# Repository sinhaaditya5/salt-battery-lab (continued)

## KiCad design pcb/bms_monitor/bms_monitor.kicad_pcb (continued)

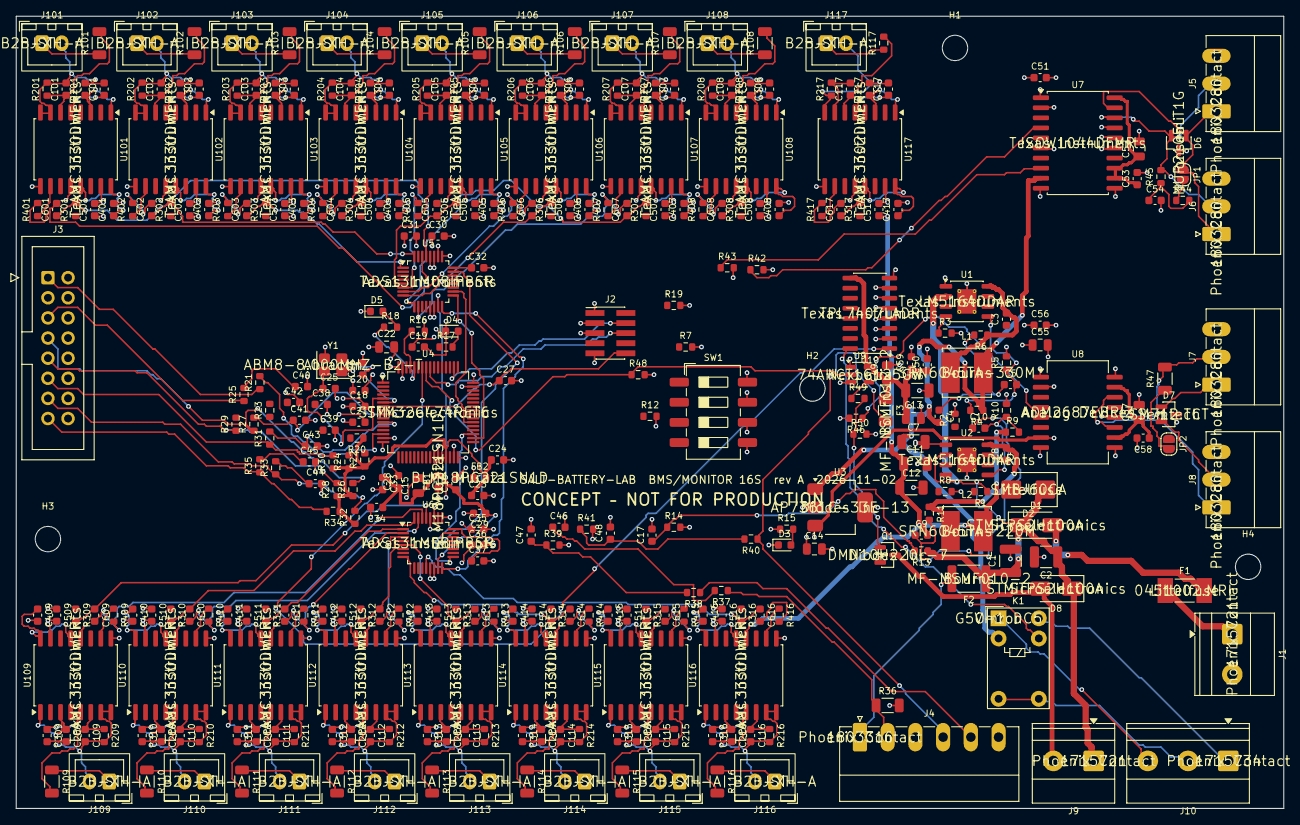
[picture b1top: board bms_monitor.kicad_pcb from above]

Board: 4 copper layers, 160.0 x 100.0 mm, 358 parts (0 on the bottom side), 272 nets.

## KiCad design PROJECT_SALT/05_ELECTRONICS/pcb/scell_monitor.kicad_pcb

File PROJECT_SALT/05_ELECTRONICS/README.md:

# Electronics: SCM-1 salt-cell test monitor (designed for the S-cell chemistry and voltage)

| Item | Status |
|---|---|
| Schematic (`kicad/`, `schematics/`) | 145 parts, 94 nets; **ERC 0 violations** (MAX31856 pin types corrected to datasheet: SDO tri-state, FAULT open-drain, in `scm_pcb.kicad_sym`) |
| PCB (`pcb/`) | 4-layer, 110 × 75 mm; auto-placed, auto-routed **DRAFT**: 1,703 tracks, 37 unrouted connections, 178 clearance errors → **not for fabrication** |
| Gerbers / drill / pick-and-place (`gerbers/`) | exported from the draft, **for review only** |
| BOM (`bom/`) | grouped, with manufacturer part numbers |
| Firmware (`firmware/`) | supervision core + MAX31856 driver + main loop. `make test`: **19/19 core checks, 0 driver failures, main loop syntax-clean under -Werror**. HAL, ADS131M08 and INA228 drivers not written |
| Electrical test procedure | `07_BUILD_MANUAL/acceptance_tests/ELECTRICAL_TEST_PROCEDURE.md` (TP-E01…E06) |

**Design basis** (`params/scell_params.py`, generated `firmware/limits.h`):
- 1.65 / 2.95 V cell trips (inside the 1.58 / 3.05 V side reactions);
- 290 °C hardware thermocouple trip;
- 2 °C/min ramp limit;
- 181 mA (40 mA/cm²) over-current trip.

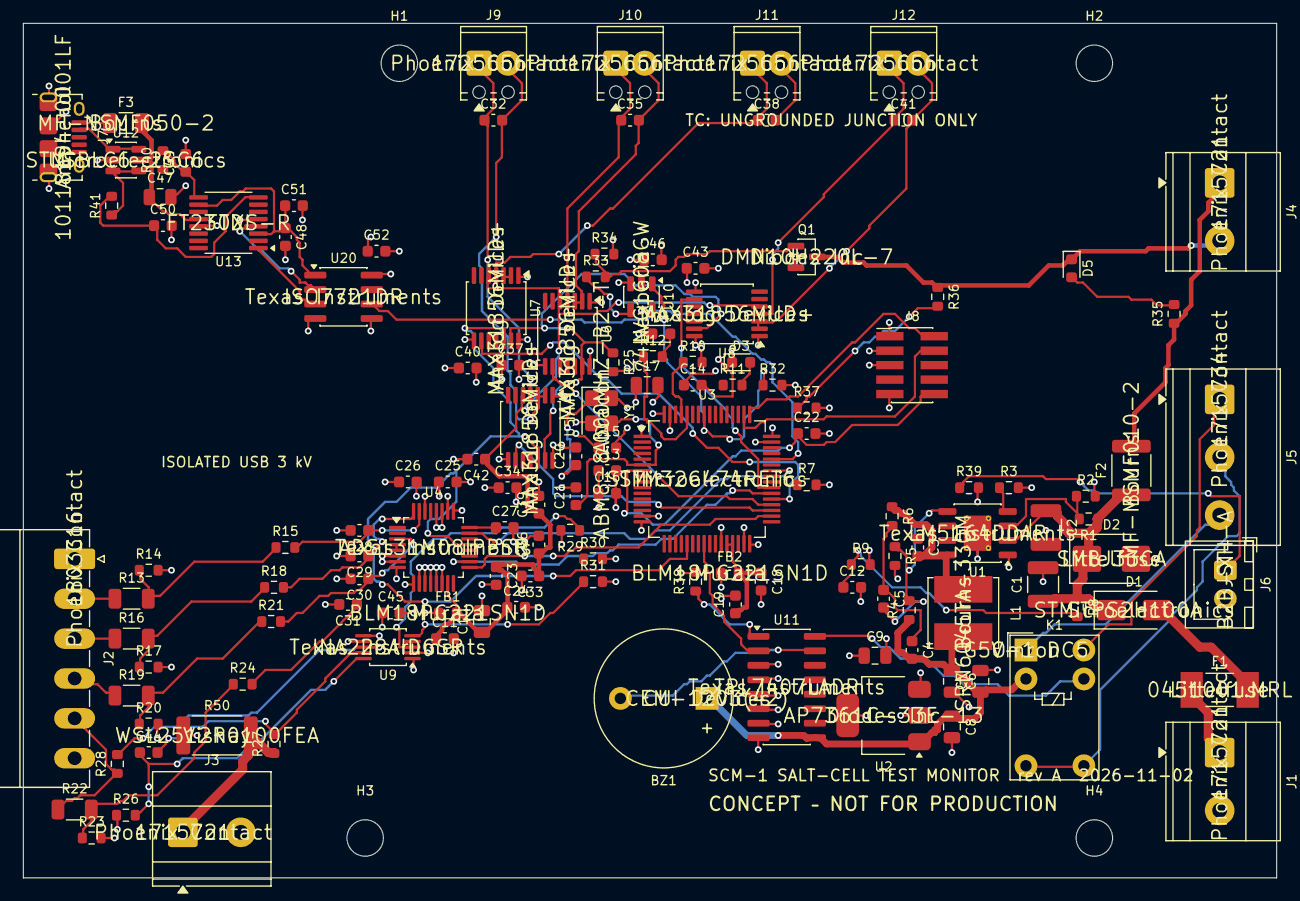
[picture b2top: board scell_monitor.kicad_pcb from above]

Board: 4 copper layers, 110.0 x 75.0 mm, 139 parts (0 on the bottom side), 94 nets.

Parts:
BZ1: CEM-1203(42); Buzzer_12x9.5RM7.6
C1, C2: 2.2u 100V; C_1210_3225Metric
C3: 2.2n; C_0603_1608Metric
C4: 3.3n; C_0603_1608Metric
C5: 56p C0G; C_0603_1608Metric
C6, C7: 22u 10V; C_0805_2012Metric
C8, C9, C10: 10u; C_0805_2012Metric
C11, C12, C13, C14, C15, C16, C19, C22, C24, C26, C33, C34, C36, C37, C39, C40, C42, C43, C45, C46, C48, C51, C52: 100n; C_0603_1608Metric
C17, C47: 4.7u; C_0805_2012Metric
C18, C23, C25: 1u; C_0603_1608Metric
C20, C21: 27p C0G; C_0603_1608Metric
C27: 220n; C_0603_1608Metric
C28, C29, C30, C31: 100n C0G; C_0603_1608Metric
C32, C35, C38, C41, C44: 10n C0G; C_0603_1608Metric
C49, C50: 47p C0G; C_0603_1608Metric
D1: STPS2H100A; D_SMA
D2: SMBJ33CA; D_SMB
D3: green RUN; LED_0603_1608Metric
D4: red FAULT; LED_0603_1608Metric
D5: amber HEAT; LED_0603_1608Metric
F1: 1A; Fuse_Littelfuse-NANO2-451_453
F2: MF-MSMF010-2; Fuse_1812_4532Metric
F3: MF-NSMF050-2; Fuse_1206_3216Metric
FB1, FB2: BLM18PG221SN1D; L_0603_1608Metric
H1, H2, H3, H4: M3; MountingHole_3.2mm_M3
J1: PWR_IN 12-30V; TerminalBlock_Phoenix_MKDS-1,5-2-5.08_1x02_P5.08mm_Horizont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
J2: CELL TAPS; PhoenixContact_MC_1,5_6-G-3.5_1x06_P3.50mm_Horizontal
J3: CYCLER -; TerminalBlock_Phoenix_MKDS-1,5-2-5.08_1x02_P5.08mm_Horizont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
J4: SSR CTRL; TerminalBlock_Phoenix_MKDS-1,5-2-5.08_1x02_P5.08mm_Horizont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
J5: CYCLER INTERLOCK; TerminalBlock_Phoenix_MKDS-1,5-3-5.08_1x03_P5.08mm_Horizont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
J6: E-STOP sense; JST_XH_B2B-XH-A_1x02_P2.50mm_Vertical
J7: USB; USB_Micro-B_Amphenol_10118194_Horizontal
J8: SWD; PinHeader_2x05_P1.27mm_Vertical_SMD
J9: TC1 type-K; TerminalBlock_Phoenix_MPT-0,5-2-2.54_1x02_P2.54mm_Horizontal
J10: TC2 type-K; TerminalBlock_Phoenix_MPT-0,5-2-2.54_1x02_P2.54mm_Horizontal
J11: TC3 type-K; TerminalBlock_Phoenix_MPT-0,5-2-2.54_1x02_P2.54mm_Horizontal
J12: TC4 type-K; TerminalBlock_Phoenix_MPT-0,5-2-2.54_1x02_P2.54mm_Horizontal
K1: G5V-1-DC5; Relay_SPDT_Omron_G5V-1
L1: 33u; L_Bourns_SRN6045TA
Q1: DMN10H220L; SOT-23
R1: 432k; R_0603_1608Metric
R2, R32, R34, R36, R38: 100k; R_0603_1608Metric
R3: 31.6k; R_0603_1608Metric
R4: 158k; R_0603_1608Metric
R5: 49.9k; R_0603_1608Metric
R6: 165k; R_0603_1608Metric
R7, R9, R10, R25, R29, R35, R37, R39: 10k; R_0603_1608Metric
R8: 200k; R_0603_1608Metric
R11, R12, R15, R18, R21, R24, R28: 1k; R_0603_1608Metric
R13, R16, R19, R22: 100k 0.1%; R_1206_3216Metric
R14, R17, R20, R23: 10k 0.1%; R_0603_1608Metric
R26, R27: 10R; R_0603_1608Metric
R30, R31: 4.7k; R_0603_1608Metric
R33: 100R; R_0603_1608Metric
R40, R41: 27R; R_0603_1608Metric
R50: 10m 1% 3W; R_2512_6332Metric
U1: LM5164DDA; HSOP-8-1EP_3.9x4.9mm_P1.27mm_EP2.41x3.1mm_ThermalVias
U2: AP7361C-33E; SOT-223-3_TabPin2
U3: STM32G474RET6; LQFP-64_10x10mm_P0.5mm
U4: ADS131M08IPBS; TQFP-32_5x5mm_P0.5mm
U5, U6, U7, U8: MAX31856MUD; TSSOP-14_4.4x5mm_P0.65mm
U9: INA228AIDGSR; TSSOP-10_3x3mm_P0.5mm
U10: 74LVC1G08; SOT-23-5
U11: TPL7407LAD; SOIC-16_3.9x9.9mm_P1.27mm
U12: USBLC6-2SC6; SOT-23-6
U13: FT230XS; SSOP-16_3.9x4.9mm_P0.635mm
U20: ISO7721DR; SOIC-8_3.9x4.9mm_P1.27mm
Y1: 8MHz; Crystal_SMD_3225-4Pin_3.2x2.5mm

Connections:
+3V3: C9.1, C13.1, C14.1, C15.1, C16.1, C17.1, C25.1, C26.1, C34.1, C37.1, C40.1, C43.1, C45.1, C46.1, C52.1, FB1.1, FB2.1, J8.1, R7.2, R25.2, R29.2, R30.2, R31.2, R39.2, U2.3, U3.1, U3.16, U3.32, U3.48, U3.64, U4.26, U5.8, U6.8, U7.8, U8.8, U9.6, U10.5, U20.8
+3V3_ADC: C10.1, C11.1, C23.1, C24.1, C33.1, C36.1, C39.1, C42.1, FB1.2, U4.15, U5.5, U6.5, U7.5, U8.5
+5V: BZ1.1, C4.2, C6.1, C7.1, C8.1, K1.2, L1.2, R4.1, U2.1, U11.9
A1: C28.1, R15.2, U4.29, U4.31
A2: C29.1, R18.2, U4.2, U4.32
A3: C30.1, R21.2, U4.1, U4.3
A4: C31.1, R24.2, U4.4, U4.5
ADC_CAP: C27.1, U4.24
ADC_CLK: U3.42, U4.23
ADC_CS: U3.34, U4.17
ADC_DRDY: U3.38, U4.18
ADC_SYNC: U3.52, U4.16
BOOT0: R10.1, U3.61
BST1: C3.1, U1.7
BUZ_EN: U3.24, U11.2
BUZ_N: BZ1.2, U11.15
CYC_NEG: J3.1, R27.1, R50.2
EN_UVLO: R1.2, R2.1, U1.3
ESTOP_SNS: J6.1, R39.1, U3.54
FB1: C5.2, R4.2, R5.1, U1.5
GND: C1.2, C2.2, C6.2, C7.2, C8.2, C9.2, C10.2, C11.2, C12.2, C13.2, C14.2, C15.2, C16.2, C17.2, C18.2, C19.2, C20.2, C21.2, C22.2, C23.2, C24.2, C25.2, C26.2, C27.2, C28.2, C29.2, C30.2, C31.2, C33.2, C34.2, C36.2, C37.2, C39.2, C40.2, C42.2, C43.2, C45.2, C46.2, C52.2, D2.2, D3.1, D4.1, J1.2, J2.1, J2.6, J3.2, J6.2, J8.3, J8.5, J8.9, Q1.2, R2.2, R3.2, R5.2, R9.2, R10.2, R14.2, R17.2, R20.2, R23.2, R26.1, R32.2, R34.2, R37.2, R38.2, R50.1, U1.1, U1.9, U2.2, U3.15, U3.27, U3.31, U3.47, U3.63, U4.6, U4.7, U4.8, U4.9, U4.10, U4.11, U4.12, U4.13, U4.14, U4.25, U4.27, U4.28, U4.30, U5.1, U5.14, U6.1, U6.14, U7.1, U7.14, U8.1, U8.14, U9.1, U9.2, U9.7, U10.3, U11.3, U11.4, U11.5, U11.6, U11.7, U11.8, U20.5, Y1.2, Y1.4
HEAT_EN: R32.1, U3.57, U10.1
HEAT_FB: R36.2, R37.1, U3.12
HEAT_G: Q1.1, R33.2, R34.1
HEAT_GATE: R33.1, U10.4
I2C_SCL: R31.1, U3.40, U9.5
I2C_SDA: R30.1, U3.41, U9.4
ILK_COM: J5.2, K1.5, K1.6
ILK_EN: R38.1, U3.58, U11.1
ILK_NC: J5.3, K1.1
ILK_NO: J5.1, K1.10
INA_ALERT: R29.1, U3.53, U9.3
IUSB_3V3: C48.1, C51.1, U13.3, U13.10, U20.1
IUSB_DM: J7.2, R40.1, U12.1, U12.6
IUSB_DP: J7.3, R41.1, U12.3, U12.4
IUSB_FDM: C49.1, R40.2, U13.9
IUSB_FDP: C50.1, R41.2, U13.8
IUSB_GND: C47.2, C48.2, C49.2, C50.2, C51.2, J7.5, J7.SH, U12.2, U13.5, U13.13, U20.4
IUSB_RXD: U13.4, U20.2
IUSB_TXD: U13.1, U20.3
IUSB_VBUS: C47.1, F3.2, U12.5, U13.12
IUSB_VBUS_RAW: F3.1, J7.1
LED_FLT: R12.1, U3.60
LED_FLT_A: D4.2, R12.2
LED_HEAT_A: D5.2, R35.2
LED_RUN: R11.1, U3.59
LED_RUN_A: D3.2, R11.2
NRST: C22.1, J8.10, U3.7
OSC_IN: C20.1, U3.5, Y1.1
OSC_OUT: C21.1, U3.6, Y1.3
PG_5V: R7.1, U1.6, U3.2
RIP1: C4.1, C5.1, R6.2
RLY_COIL: K1.9, U11.16
RON1: R3.1, U1.4
SH_N: C44.2, R27.2, U9.9
SH_P: C44.1, R26.2, U9.10
SPI_MISO: U3.20, U4.20, U5.11, U6.11, U7.11, U8.11
SPI_MOSI: U3.21, U4.21, U5.12, U6.12, U7.12, U8.12
SPI_SCK: U3.19, U4.19, U5.10, U6.10, U7.10, U8.10
SSR_NEG: D5.1, J4.2, Q1.3, R36.1
SSR_POS: F2.2, J4.1, R35.1
SW1: C3.2, L1.1, R6.1, U1.8
SWCLK: J8.4, U3.50
SWDIO: J8.2, U3.49
SWO: J8.6, U3.56
TAP1: J2.2, R13.1
TAP2: J2.3, R16.1
TAP3: J2.4, R19.1
TAP4: J2.5, R22.1, R28.1
TC1_N: C32.2, J9.2, U5.2, U5.3
TC1_P: C32.1, J9.1, U5.4
TC2_N: C35.2, J10.2, U6.2, U6.3
TC2_P: C35.1, J10.1, U6.4
TC3_N: C38.2, J11.2, U7.2, U7.3
TC3_P: C38.1, J11.1, U7.4
TC4_N: C41.2, J12.2, U8.2, U8.3
TC4_P: C41.1, J12.1, U8.4
TC_CS1: U3.35, U5.9
TC_CS2: U3.36, U6.9
TC_CS3: U3.37, U7.9
TC_CS4: U3.39, U8.9
TC_FAULT_N: R25.1, U3.25, U5.13, U6.13, U7.13, U8.13, U10.2
TS1: R13.2, R14.1, R15.1
TS2: R16.2, R17.1, R18.1
TS3: R19.2, R20.1, R21.1
TS4: R22.2, R23.1, R24.1
UART_RX: U3.44, U20.6
UART_TX: U3.43, U20.7
VBUS_S: R28.2, U9.8
VDDA: C18.1, C19.1, FB2.2, U3.28, U3.29
VIN_F: D1.2, F1.2
VIN_P: C1.1, C2.1, D1.1, D2.1, F2.1, R1.1, R8.1, U1.2
VIN_RAW: F1.1, J1.1
VIN_SNS: C12.1, R8.2, R9.1, U3.26

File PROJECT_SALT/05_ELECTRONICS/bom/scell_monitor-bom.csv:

"Reference","Value","Footprint","MPN","Manufacturer","QUANTITY"
"BZ1","CEM-1203(42)","Buzzer_Beeper:Buzzer_12x9.5RM7.6","CEM-1203(42)","CUI Devices","1"
"C1,C2","2.2u 100V","Capacitor_SMD:C_1210_3225Metric","","","2"
"C3","2.2n","Capacitor_SMD:C_0603_1608Metric","","","1"
"C4","3.3n","Capacitor_SMD:C_0603_1608Metric","","","1"
"C5","56p C0G","Capacitor_SMD:C_0603_1608Metric","","","1"
"C6,C7","22u 10V","Capacitor_SMD:C_0805_2012Metric","","","2"
"C8-C10","10u","Capacitor_SMD:C_0805_2012Metric","","","3"
"C11-C16,C19,C22,C24,C26,C33,C34,C36,C37,C39,C40,C42,C43,C45,C46,C48,C51,C52","100n","Capacitor_SMD:C_0603_1608Metric","","","23"
"C17,C47","4.7u","Capacitor_SMD:C_0805_2012Metric","","","2"
"C18,C23,C25","1u","Capacitor_SMD:C_0603_1608Metric","","","3"
"C20,C21","27p C0G","Capacitor_SMD:C_0603_1608Metric","","","2"
"C27","220n","Capacitor_SMD:C_0603_1608Metric","","","1"
"C28-C31","100n C0G","Capacitor_SMD:C_0603_1608Metric","","","4"
"C32,C35,C38,C41,C44","10n C0G","Capacitor_SMD:C_0603_1608Metric","","","5"
"C49,C50","47p C0G","Capacitor_SMD:C_0603_1608Metric","","","2"
"D1","STPS2H100A","Diode_SMD:D_SMA","STPS2H100A","STMicroelectronics","1"
"D2","SMBJ33CA","Diode_SMD:D_SMB","SMBJ33CA","Littelfuse","1"
"D3","green RUN","LED_SMD:LED_0603_1608Metric","","","1"
"D4","red FAULT","LED_SMD:LED_0603_1608Metric","","","1"
"D5","amber HEAT","LED_SMD:LED_0603_1608Metric","","","1"
"F1","1A","Fuse:Fuse_Littelfuse-NANO2-451_453","0451001.MRL","Littelfuse","1"
"F2","MF-MSMF010-2","Fuse:Fuse_1812_4532Metric","MF-MSMF010-2","Bourns","1"
"F3","MF-NSMF050-2","Fuse:Fuse_1206_3216Metric","MF-NSMF050-2","Bourns","1"
"FB1,FB2","BLM18PG221SN1D","Inductor_SMD:L_0603_1608Metric","BLM18PG221SN1D","Murata","2"
"H1-H4","M3","MountingHole:MountingHole_3.2mm_M3","","","4"
"J1","PWR_IN 12-30V","TerminalBlock_Phoenix:TerminalBlock_Phoenix_MKDS-1,5-2-5.08_1x02_P5.08mm_Horizontal","1715721","Phoenix Contact","1"
"J2","CELL TAPS","Connector_Phoenix_MC:PhoenixContact_MC_1,5_6-G-3.5_1x06_P3.50mm_Horizontal","1803316","Phoenix Contact","1"
"J3","CYCLER -","TerminalBlock_Phoenix:TerminalBlock_Phoenix_MKDS-1,5-2-5.08_1x02_P5.08mm_Horizontal","1715721","Phoenix Contact","1"
"J4","SSR CTRL","TerminalBlock_Phoenix:TerminalBlock_Phoenix_MKDS-1,5-2-5.08_1x02_P5.08mm_Horizontal","1715721","Phoenix Contact","1"
"J5","CYCLER INTERLOCK","TerminalBlock_Phoenix:TerminalBlock_Phoenix_MKDS-1,5-3-5.08_1x03_P5.08mm_Horizontal","1715734","Phoenix Contact","1"
"J6","E-STOP sense","Connector_JST:JST_XH_B2B-XH-A_1x02_P2.50mm_Vertical","B2B-XH-A","JST","1"
"J7","USB","Connector_USB:USB_Micro-B_Amphenol_10118194_Horizontal","10118194-0001LF","Amphenol","1"
"J8","SWD","Connector_PinHeader_1.27mm:PinHeader_2x05_P1.27mm_Vertical_SMD","","","1"
"J9","TC1 type-K","TerminalBlock_Phoenix:TerminalBlock_Phoenix_MPT-0,5-2-2.54_1x02_P2.54mm_Horizontal","1725656","Phoenix Contact","1"
"J10","TC2 type-K","TerminalBlock_Phoenix:TerminalBlock_Phoenix_MPT-0,5-2-2.54_1x02_P2.54mm_Horizontal","1725656","Phoenix Contact","1"
"J11","TC3 type-K","TerminalBlock_Phoenix:TerminalBlock_Phoenix_MPT-0,5-2-2.54_1x02_P2.54mm_Horizontal","1725656","Phoenix Contact","1"
"J12","TC4 type-K","TerminalBlock_Phoenix:TerminalBlock_Phoenix_MPT-0,5-2-2.54_1x02_P2.54mm_Horizontal","1725656","Phoenix Contact","1"
"K1","G5V-1-DC5","Relay_THT:Relay_SPDT_Omron_G5V-1","G5V-1 DC5","Omron","1"
"L1","33u","Inductor_SMD:L_Bourns_SRN6045TA","SRN6045TA-330M","Bourns","1"
"Q1","DMN10H220L","Package_TO_SOT_SMD:SOT-23","DMN10H220L-7","Diodes Inc","1"
"R1","432k","Resistor_SMD:R_0603_1608Metric","","","1"
"R2,R32,R34,R36,R38","100k","Resistor_SMD:R_0603_1608Metric","","","5"
"R3","31.6k","Resistor_SMD:R_0603_1608Metric","","","1"
"R4","158k","Resistor_SMD:R_0603_1608Metric","","","1"
"R5","49.9k","Resistor_SMD:R_0603_1608Metric","","","1"
"R6","165k","Resistor_SMD:R_0603_1608Metric","","","1"
"R7,R9,R10,R25,R29,R35,R37,R39","10k","Resistor_SMD:R_0603_1608Metric","","","8"
"R8","200k","Resistor_SMD:R_0603_1608Metric","","","1"
"R11,R12,R15,R18,R21,R24,R28","1k","Resistor_SMD:R_0603_1608Metric","","","7"
"R13,R16,R19,R22","100k 0.1%","Resistor_SMD:R_1206_3216Metric","","","4"
"R14,R17,R20,R23","10k 0.1%","Resistor_SMD:R_0603_1608Metric","","","4"
"R26,R27","10R","Resistor_SMD:R_0603_1608Metric","","","2"
"R30,R31","4.7k","Resistor_SMD:R_0603_1608Metric","","","2"
"R33","100R","Resistor_SMD:R_0603_1608Metric","","","1"
"R40,R41","27R","Resistor_SMD:R_0603_1608Metric","","","2"
"R50","10m 1% 3W","Resistor_SMD:R_2512_6332Metric","WSL2512R0100FEA","Vishay","1"
"U1","LM5164DDA","Package_SO:HSOP-8-1EP_3.9x4.9mm_P1.27mm_EP2.41x3.1mm_ThermalVias","LM5164DDAR","Texas Instruments","1"
"U2","AP7361C-33E","Package_TO_SOT_SMD:SOT-223-3_TabPin2","AP7361C-33E-13","Diodes Inc","1"
"U3","STM32G474RET6","Package_QFP:LQFP-64_10x10mm_P0.5mm","STM32G474RET6","STMicroelectronics","1"
"U4","ADS131M08IPBS","Package_QFP:TQFP-32_5x5mm_P0.5mm","ADS131M08IPBSR","Texas Instruments","1"
"U5-U8","MAX31856MUD","Package_SO:TSSOP-14_4.4x5mm_P0.65mm","MAX31856MUD+","Analog Devices","4"
"U9","INA228AIDGSR","Package_SO:TSSOP-10_3x3mm_P0.5mm","INA228AIDGSR","Texas Instruments","1"
"U10","74LVC1G08","Package_TO_SOT_SMD:SOT-23-5","74LVC1G08GW","Nexperia","1"
"U11","TPL7407LAD","Package_SO:SOIC-16_3.9x9.9mm_P1.27mm","TPL7407LADR","Texas Instruments","1"
"U12","USBLC6-2SC6","Package_TO_SOT_SMD:SOT-23-6","USBLC6-2SC6","STMicroelectronics","1"
"U13","FT230XS","Package_SO:SSOP-16_3.9x4.9mm_P0.635mm","FT230XS-R","FTDI","1"
"U20","ISO7721DR","Package_SO:SOIC-8_3.9x4.9mm_P1.27mm","ISO7721DR","Texas Instruments","1"
"Y1","8MHz","Crystal:Crystal_SMD_3225-4Pin_3.2x2.5mm","ABM8-8.000MHZ-B2-T","Abracon","1"

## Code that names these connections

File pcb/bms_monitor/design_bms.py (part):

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
    # ---------------------------------------------------------------- MCU
    mcu = {"VBAT": "+3V3", "VDD": "+3V3", "VSS": "GND", "VSSA": "GND", "VDDA": "VDDA", "VREF+": "VDDA",
           "PF0": "OSC_IN", "PF1": "OSC_OUT", "PG10": "NRST",
           "PA0": "I_ADCP", "PA1": "I_ADCN", "PA2": "NTC1_ADC", "PA3": "NTC2_ADC",
           "PC0": "NTC3_ADC", "PC1": "NTC4_ADC", "PC2": "NTC5_ADC", "PC3": "NTC6_ADC", "PB0": "NTC7_ADC", "PB1": "NTC8_ADC",
           "PA4": "H2_ADC", "PC4": "PRESS_ADC", "PC5": "P5V_ADC", "PB2": "VIN_SNS",
           "PA5": "SPI_SCK", "PA6": "SPI_MISO", "PA7": "SPI_MOSI", "PA8": "ADC_CLK",
           "PB12": "ADC_CS1", "PB13": "ADC_CS2", "PC6": "ADC_DRDY1", "PC7": "ADC_DRDY2", "PC8": "ADC_SYNC",
           "PA11": "CAN_RX", "PA12": "CAN_TX", "PC9": "CAN_STB", "PC10": "CAN_FLT",
           "PB10": "RS485_TX", "PB11": "RS485_RX", "PB14": "RS485_DE",
           "PA13": "SWDIO", "PA14": "SWCLK", "PB3": "SWO",
           "PB4": "CONT_EN", "PB5": "ALARM_EN", "PB6": "LED_RUN", "PB7": "LED_FLT", "PB8": "BOOT0",
           "PA15": "ADDR0", "PC11": "ADDR1", "PC12": "ADDR2", "PD2": "ADDR3",
           "PB15": "AMC_DIAG", "PC13": "PG_5V", "PB9": "PG_3V3A",
           "PA9": None, "PA10": None, "PC14": None, "PC15": None}
    d.add(M, "MCU_ST_STM32G4:STM32G474RETx", "STM32G474RET6", mcu, ref="U4",
          MPN="STM32G474RET6", Manufacturer="STMicroelectronics", Notes="Cortex-M4 170 MHz, FDCAN (CAN 2.0B/FD), 5x12-bit ADC")
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    Cc(M, "1u", "VDDA", "GND"); Cc(M, "100n", "VDDA", "GND")
    d.add(M, "Device:Crystal_GND24", "8MHz", {"1": "OSC_IN", "3": "OSC_OUT", "2": "GND"},
          footprint="Crystal:Crystal_SMD_3225-4Pin_3.2x2.5mm", ref="Y1", MPN="ABM8-8.000MHZ-B2-T", Manufacturer="Abracon",
          Notes="CL 18 pF; HSE also clocks both ADS131M08 via MCO (PA8)")
    Cc(M, "27p C0G", "OSC_IN", "GND"); Cc(M, "27p C0G", "OSC_OUT", "GND")
    R(M, "10k", "BOOT0", "GND"); Cc(M, "100n", "NRST", "GND")
    d.add(M, "Connector_Generic:Conn_02x05_Odd_Even", "SWD", {"1": "+3V3", "2": "SWDIO", "3": "GND", "4": "SWCLK", "5": "GND",
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    d.notes["cells0"] = ["Each channel: block terminals -> 1 M / 30.1 k (0.1 %) divider + 100 nF -> AMC3330 (gain 2) -> RC -> ADS131M08.",
                         "Channel k HGND = block k negative terminal.  Full scale %.0f V -> %.3f V AMC input -> %.3f V ADC (FSR 1.2 V)."
                         % (V_BLOCK_FS, V_BLOCK_FS * DIV, V_BLOCK_FS * DIV * 2)]
    d.notes["current"] = ["Shunt %.2f mOhm x %d A = %.0f mV = AMC3302 linear full scale; output to STM32 ADC1 differential (PA0/PA1)."
                          % (SHUNT_MOHM, I_MAX, V_SHUNT_FS * 1000)]
    d.notes["power"] = ["9-60 V in: 2 A fuse, STPS2H100A series diode (reverse polarity), SMBJ60CA TVS, two LM5164 (100 V) bucks:",
                        "+5V (comms DC/DC, sensors, relay) and +3V3A (17 isolated amplifiers, ~0.5 A typ); AP7361C LDO +3V3 logic."]
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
